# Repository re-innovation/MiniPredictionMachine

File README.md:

# MiniPredictionMachine
Arduino based weather sensor unit with solar PV charing and an ESP8266 based receiver unit

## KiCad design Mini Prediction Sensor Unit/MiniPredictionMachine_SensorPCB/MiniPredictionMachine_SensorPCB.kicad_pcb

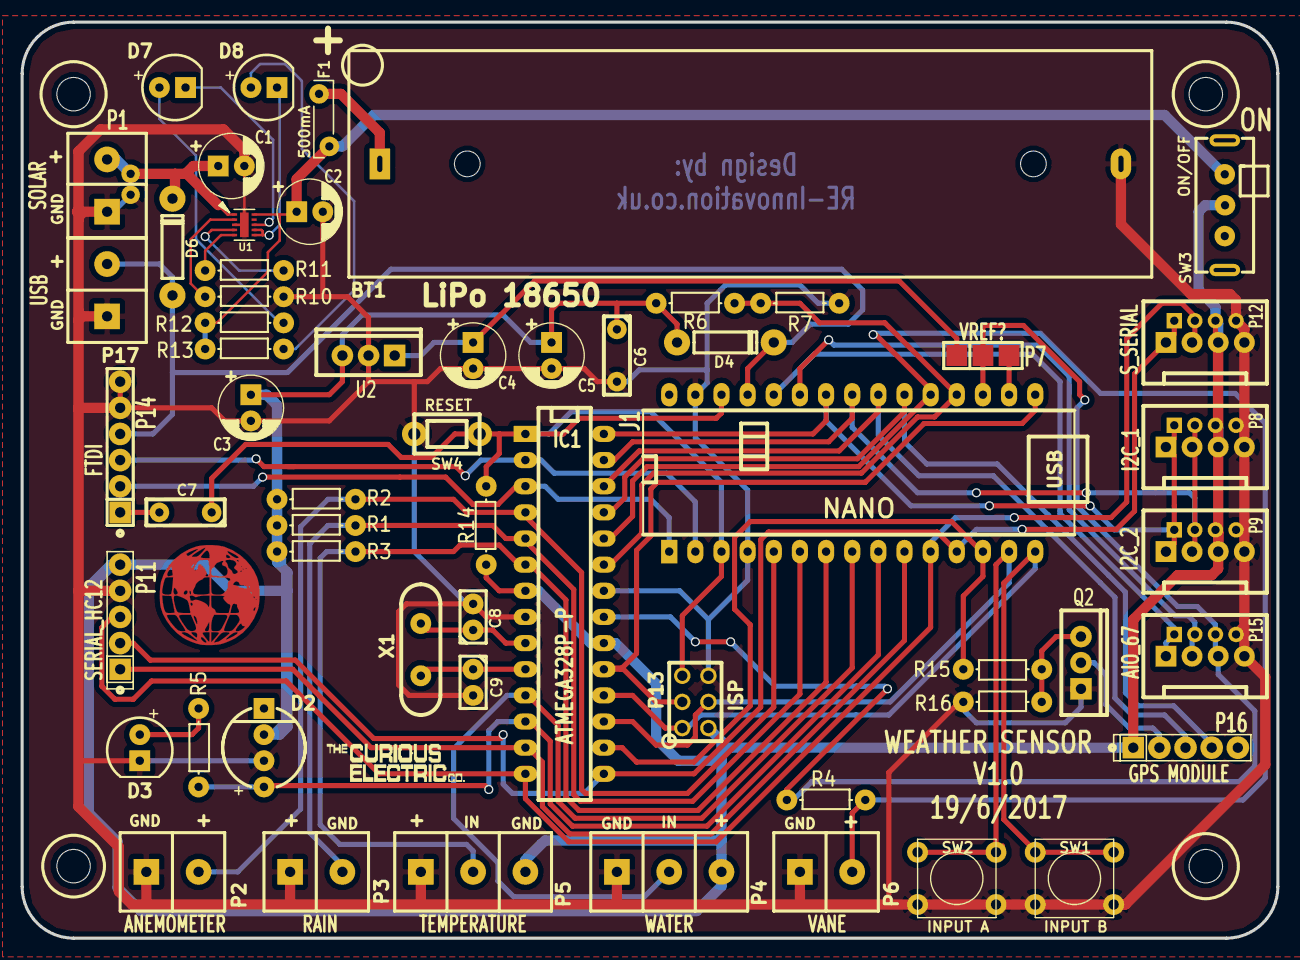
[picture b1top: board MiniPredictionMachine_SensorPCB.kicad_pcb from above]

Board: 2 copper layers, 122.0 x 89.0 mm, 60 parts (0 on the bottom side), 45 nets.

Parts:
BT1: LiPo 18650; TH_LiIon_Holder
C1, C2: 1uF; C_1V7_TH
C3, C4: 10uF; C_1V7_TH
C5: 100uF; C_1V7_TH
C6, C7: 100nF; C1_wide_lg_pad
C8, C9: 22pF; C1_lg_pad
D2: LED; TH_WS2811_LED_8mm
D3: DATA; TH_LED-5MM_larg_pad
D4, D6: D_Schottky; TH_Diode_1
D7: CHG; TH_LED-5MM_larg_pad
D8: PG; TH_LED-5MM_larg_pad
F1: 500mA; TH_MC36188_FUSE
IC1: ATMEGA328P-P; DIP-28__300_ELL
J1: NANO; NANO_DIP_30_600
LOGO1: CONN_1; CEC_Globe_10mm_FCU
LOGO2: CONN_1; TCEC_Words_13mm
P1: SOLAR; SIL_2_screw_+_JST_2mm
P2: ANEMOMETER; SIL-2_screw_terminal
P3: RAIN; SIL-2_screw_terminal
P4: WATER; SIL-3_screw_terminal
P5: TEMPERATURE; SIL-3_screw_terminal
P6: VANE; SIL-2_screw_terminal
P7: VREF?; SIL-3_solder_connect
P8: I2C_1; SIL-4_Grove_SIL
P9: I2C_2; SIL-4_Grove_SIL
P11: SERIAL_HC12; SIL-5_large_pads_marker
P12: S_SERIAL; SIL-4_Grove_SIL
P13: ISP; ISP_3x2
P14: FTDI; SIL-6_large_pads_marker
P15: AIO_67; SIL-4_Grove_SIL
P16: GPS MODULE; SIL-5_large_pads_marker
P17: USB; SIL-2_screw_terminal
PCB1: CONN_1; PCB_85x120_4hole_EdgeCut
Q2: BD135; TO220_BD135
R1, R2, R4, R14: 10k; TH_Resistor_1
R3: 4k7; TH_Resistor_1
R5: 330; TH_Resistor_1
R6, R7, R11, R16: 100k; TH_Resistor_1
R10, R15: 1k; TH_Resistor_1
R12, R13: 2.2k; TH_Resistor_1
SW1: INPUT B; SW_PUSH_SMALL_lg_pad
SW2: INPUT A; SW_PUSH_SMALL_lg_pad
SW3: ON/OFF; SW_SPDT_R_Angle_ALIEX
SW4: RESET; SW_PUSH_single_pins
U1: BQ24210; SM_WSON-10-2x3
U2: MCP1826S; TO220_MCP1826S
X1: 16MHz; Xtal_small_matt

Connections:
+3.3V: IC1.21, J1.18, P7.2, P15.3, R4.1
/A6: J1.25, P15.2
/A7: J1.26, P15.1
/Arduino Nano or IC/3V3_NANO: J1.17, P7.3
/Arduino Nano or IC/D13: IC1.19, J1.16, P13.3
/GPS_CS: IC1.16, J1.13, R15.2
/LED_WS2811: D2.4, IC1.12, J1.9, R5.2
/MOISTURE: IC1.11, J1.8, P4.2
/RAIN_FALL: IC1.5, J1.6, P3.2, R1.2
/Rx: IC1.2, J1.2, P14.3
/Rx_SOFT: IC1.15, J1.12, P11.2, P12.1
/Rx_SOFT2: IC1.26, J1.22, P16.3
/SCLK: IC1.28, J1.24, P8.1, P9.1
/SDA: IC1.27, J1.23, P8.2, P9.2
/SW_A: IC1.17, J1.14, P13.4, SW2.1
/SW_B: IC1.18, J1.15, P13.1, SW1.1
/Solar Charging/3V3: C4.1, P7.1, U2.3
/Solar Charging/LiPoOUT+: BT1.1, F1.2
/Solar Charging/PVIN+: C1.1, D6.1, P1.2, U1.1
/TEMPERATURE: IC1.6, J1.7, P5.2, R3.2
/Tx: IC1.3, J1.1, P14.2
/Tx_SOFT: IC1.14, J1.11, P11.3, P12.2
/Tx_SOFT2: IC1.25, J1.21, P16.4
/VANE: IC1.24, J1.20, P6.2, R4.2
/VBATT: IC1.23, J1.19, R6.2, R7.1
/VUSB: D4.1, D6.2, J1.27, P14.4, P17.2
/Vss: C3.1, C5.1, C6.1, D2.2, D4.2, IC1.7, IC1.20, P4.3, P5.3, P8.3, P9.3, P11.5, P12.3, P13.2, P16.1, R1.1, R2.1, R3.1, R6.1, R14.1, SW3.2, U2.1
/WIND_SPEED: IC1.4, J1.5, P2.2, R2.2
/WIRELESS_CS: IC1.13, J1.10, P11.1
GND: BT1.2, C1.2, C2.2, C3.2, C4.2, C5.2, C6.2, C8.2, C9.2, D2.3, D3.1, IC1.8, IC1.22, J1.4, J1.29, P1.1, P2.1, P3.1, P4.1, P5.1, P6.1, P8.4, P9.4, P11.4, P12.4, P13.6, P14.5, P14.6, P15.4, P17.1, Q2.1, R7.2, R10.2, R16.1, SW1.2, SW2.2, SW4.2, U1.3, U1.PAD, U2.2
unnamed: C2.1, F1.1, R12.1, R13.1, SW3.1, U1.10
unnamed: C7.2, P14.1
unnamed: C8.1, IC1.9, X1.2
unnamed: C9.1, IC1.10, X1.1
unnamed: D3.2, R5.1
unnamed: D7.1, U1.8
unnamed: D7.2, R12.2
unnamed: D8.1, U1.6, U1.7
unnamed: D8.2, R13.2
unnamed: P16.2, Q2.2
unnamed: Q2.3, R15.1, R16.2
unnamed: R10.1, U1.2
unnamed: R11.1, U1.5
unnamed: R11.2, U1.4
RESET: C7.1, IC1.1, J1.3, J1.28, P13.5, R14.2, SW4.1

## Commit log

2018-03-12 Added PCB files
